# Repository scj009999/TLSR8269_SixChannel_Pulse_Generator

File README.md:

# 开源经颅脉冲治疗仪 - TLSR8269 六路脉冲发生器

> **为帕金森患者设计的低成本开源治疗设备**
> 
> 目标：让15万/年的治疗变成99元/台
> 
> 🙏 **"救一个人，胜造七级浮屠"**
> 
> 本项目完全开源，不收取任何形式的费用。能帮一个是一个。

## 项目背景

### 疾病现状
帕金森病是一种常见的神经退行性疾病，全球患者超过1000万，中国患者约300万。随着人口老龄化，这一数字仍在快速增长。

主要症状包括：静止性震颤、肌肉僵直、运动迟缓、姿势平衡障碍。

### 治疗现状
经颅脉冲刺激（Transcranial Pulse Stimulation, TPS）是一种新兴的非侵入性治疗方法，已被临床研究证明对改善帕金森症状有效。

**然而，商用设备价格高达1-3万元，医院治疗年费超过15万元，普通百姓难以承受。**

### 项目使命
本项目旨在通过完全开源的方式，将治疗成本降至百元级别，让每一个患者都能获得治疗机会。

**"每一个帕金森患者，无论贫富，都应该有权利获得有效的治疗。"**

## 成本对比

| 项目 | 商用设备 | 开源方案 | 节省 |
|------|----------|----------|------|
| 设备价格 | ¥15,000-30,000 | **¥19.91** | **99.87%** |
| 医院年费 | ¥150,000 | **¥0** | **100%** |
| 3年总费用 | ¥450,000+ | **¥250** | **99.94%** |
| 透明度 | 黑盒 | **完全开源** | - |
| 可定制 | 否 | **是** | - |

## 核心特性

### 低成本
- **物料成本**：< ¥200（批量可降至¥19.91）
- **开源免费**：代码、硬件设计全部开放
- **自制可行**：提供完整制作指南

### 医疗安全
- **电气隔离**：光耦隔离，5000V耐压
- **电流限制**：硬件+软件双重限流（最大2mA）
- **急停保护**：独立硬件急停按钮
- **阻抗检测**：实时监测电极接触
- **超时保护**：治疗超时自动停止

### 技术参数

#### 主控芯片：Telink TLSR8269F512
- 32位MCU，最高48MHz
- 512KB Flash，32KB SRAM
- 6路硬件PWM输出
- 低功耗蓝牙（可选）

### 脉冲输出参数
| 参数 | 范围 | 说明 |
|------|------|------|
| 频率 | 1Hz - 8MHz | 16MHz PWM时钟 |
| 占空比 | 0% - 100% | 精度0.01% |
| 相位 | 0° - 360° | 软件实现 |
| 通道数 | 6路 | PA0-PA3, PB0-PB1 (QFN32) |
| 输出电平 | 0V / VCC | CMOS输出 |

### 引脚定义（QFN48）

```
TLSR8269 (QFN48)
═══════════════════════════════════════

 ┌─────────────────┐
<<<<<<< HEAD
 PA0 │ 1  48 │ VCC
 PA1 │ 2  47 │ GND
 PA2 │ 3  46 │ PC0
 PA3 │ 4  45 │ PC1
 PA4 │ 5  44 │ PC2
 PA5 │ 6  43 │ PC3
 PB0 │ 7  42 │ PC4 ← CH4 (PWM4)
 PB1 │ 8  41 │ PC5 ← CH5 (PWM5)
=======
 PA0 │ 1  48 │ PA5 ← CH5
 PA1 │ 2  47 │ VCC
 PA2 │ 3  46 │ GND
 PA3 │ 4  45 │ PC0
 PA4 │ 5  44 │ PC1
 PA5 │ 6  43 │ PC2
 PB0 │ 7  42 │ PC3
 PB1 │ 8  41 │ PC4 ← TX (调试串口)
>>>>>>> 25da801773c8ff645ef9347320ff7b7be9e0631f
 ... │ ...   │ ...
 └─────────────────┘

脉冲输出引脚：
 CH0 → PA0 (Pin 1) - PWM0
 CH1 → PA1 (Pin 2) - PWM1
 CH2 → PA2 (Pin 3) - PWM2
 CH3 → PA3 (Pin 4) - PWM3
 CH4 → PB0 (Pin 7) - PWM4  ✅ QFN32封装
 CH5 → PB1 (Pin 8) - PWM5  ✅ QFN32封装
```

## 临床证据

### 核心研究 - 刘河生教授团队

**2026年2月《自然》(Nature) 发表**

- **发现**：帕金森病核心病变环路——"躯体认知环路"
- **效果**：治疗2周后，靶点组有效率达55.5%
- **产业化**：已获批3项国家医疗器械注册证
- **应用**：全国60余家医院，累计治疗超3000例
- **有效率**：突破70%

**新闻来源**：
- [腾讯网 - 首创!事关帕金森病治疗](https://new.qq.com/rain/a/20260205A040H500)
- [新京报 - 昌平实验室首次发现帕金森病核心致病功能环路](https://www.bjnews.com.cn/detail/1774781843129205.html)

更多证据见 [docs/EVIDENCE_COLLECTION.md](docs/EVIDENCE_COLLECTION.md)

---

## 安全设计 ⚠️

### 硬件安全
- **电流限制**：100Ω限流电阻，最大输出2mA（硬件）
- **电气隔离**：PC817光耦，5000V隔离
- **急停按钮**：独立硬件中断，最高优先级
- **看门狗**：1秒超时自动复位

### 软件安全
- **参数硬限制**：频率≤200Hz，电流≤2mA，时长≤30分钟
- **实时监测**：ADC每秒检测电流和阻抗
- **电极脱落检测**：阻抗>20kΩ自动报警
- **超时保护**：治疗超时自动停止

### ⚠️ 使用警告
1. **首次使用请在医生指导下进行**
2. **有癫痫病史者禁用**
3. **装有心脏起搏器者禁用**
4. **治疗过程中如感不适，立即按下急停按钮**
5. **禁止刺激眼眶、太阳穴、颈部区域**

### 禁忌症
- 心脏起搏器患者
- 癫痫病史
- 脑部金属植入
- 皮肤破损
- 孕妇
- 儿童（需医生指导）

## 快速开始

### 编译环境
- Telink SDK (TLSR826x BLE SDK V3.3.1+)
- Eclipse IDE 或 Makefile
- Telink Burning and Debugging Tool (BDT)

### 编译步骤
```bash
# 1. 导入工程到Eclipse
# 2. 选择芯片型号: TLSR8269F512
# 3. 编译项目
make

# 4. 生成烧录文件
# 输出: firmware.bin
```

### 烧录步骤
```bash
# 使用Telink BDT工具
# 1. 连接EVK烧录器
# 2. 选择芯片型号 TLSR8269
# 3. 加载 firmware.bin
# 4. 点击 Download
```

### 基础使用
```c
// 初始化
pulse_generator_init();

// 配置通道0: 40Hz, 50%占空比 (帕金森标准方案)
pulse_channel_config(0, 40, 5000, 0);

// 配置通道1: 40Hz, 50%占空比
pulse_channel_config(1, 40, 5000, 0);

// 使能输出
pulse_channel_enable(0);
pulse_channel_enable(1);

// 治疗20分钟后自动停止
```

## Arduino/Mixly 支持

本项目提供完整的 Arduino Core 支持，包括：

### 引脚定义 (pins_arduino.h)
- **QFN32 封装支持**：`firmware/arduino_core/TLSR8251F512ET32_pins_arduino.h`
- **作者**：束老师 (用户贡献)
- **功能**：24个可用GPIO，6路硬件PWM，6路ADC

### Arduino 库
支持图形化编程：

```cpp
#include <PulseTherapy.h>

void setup() {
    Pulse.begin();
    Pulse.setCurrentLimit(2000);  // 2mA限制
    Pulse.startTherapy(MODE_PARKINSON_STD, 20);  // 20分钟
}

void loop() {
    Pulse.update();  // 更新状态和安全检查
}
```

更多示例见 `PulseTherapy/examples/` 目录。

## 靶点定位

### 推荐治疗靶点
| 靶点 | 位置 | 功能 |
|------|------|------|
| M1 | 初级运动皮层 | 运动控制 |
| SMA | 辅助运动区 | 运动计划 |
| DLPFC | 背外侧前额叶 | 认知功能 |

### 六通道分配方案
```
方案A：双靶点双侧（推荐）
CH0-CH1 → M1 双侧 (40Hz, 50%)
CH2-CH3 → SMA 双侧 (40Hz, 50%)
CH4-CH5 → DLPFC 双侧 (20Hz, 30%)
```

详细定位方法见 `docs/TARGETING_SYSTEM.md`

## 项目结构

```
TLSR8269_SixChannel_Pulse_Generator/
├── main.c                          # 核心脉冲发生器代码
├── app_config.h                    # 芯片配置
├── Makefile                        # 编译脚本
├── README.md                       # 本文件（项目总览）
├── LICENSE                         # 开源许可证（含非商业条款）
├── DISCLAIMER.md                   # ⭐ 免责声明（必读）
├── FILE_INVENTORY.md               # 文件清单
│
├── hardware/                       # 硬件设计
│   ├── schematic.md                # 原理图和BOM
│   ├── TLSR8269_PulseGenerator_v2.kicad_sch  # KiCad原理图
│   ├── TLSR8269_Pinout_QFN32.md    # 引脚定义
│   ├── MEDICAL_POWER_DESIGN.md     # 医疗电源设计
│   ├── POWER_BOM.md                # 电源物料清单
│   └── KiCad_Import_Guide.md       # KiCad导入指南
│
├── docs/                           # 文档
│   ├── MEDICAL_SAFETY.md           # 医疗安全设计规范
│   ├── TARGETING_SYSTEM.md         # 靶点定位系统
│   ├── OPEN_SOURCE_LETTER.md       # 致国家药监局公开信
│   ├── COST_ANALYSIS.md            # 成本分析（目标<¥100）
│   ├── EVIDENCE_COLLECTION.md      # ⭐ 临床证据收集
│   ├── NMPA_EMAIL_DRAFT.md         # ⭐ 药监局邮件草稿
│   ├── DOCTOR_RECRUITMENT.md       # ⭐ 医生志愿者招募
│   ├── MOBILE_APP_DESIGN.md        # ⭐ 手机APP设计
│   ├── HUAQIU_AI_GUIDE.md          # 华秋AI使用指南
│   ├── HUAQIU_PRODUCTION_GUIDE.md  # 华秋生产指南
│   ├── SHELL_DESIGN_GUIDE.md       # 3D外壳设计指南
│   ├── ELECTRODE_DESIGN.md         # 头戴式电极设计
│   ├── POWER_CONTROL_COMPARISON.md # 功率调节方案对比
│   └── GITHUB_PROMOTION_GUIDE.md   # 仓库推广指南
│
├── examples/                       # 示例代码
│   ├── uart_control.c              # 串口控制示例
│   └── ...
│
├── PulseTherapy/                   # Arduino库
│   ├── PulseTherapy.h
│   ├── PulseTherapy.cpp
│   ├── keywords.txt
│   └── examples/
│       └── ParkinsonTherapy/
│           └── ParkinsonTherapy.ino
│
└── mixly_blocks/                   # Mixly图形化积木
    ├── blocks.js
    └── generator.js
```

## 成本分析

### 物料清单（BOM）
| 元件 | 型号 | 数量 | 单价(¥) | 小计(¥) |
|------|------|------|---------|---------|
| 主控芯片 | TLSR8269F512 | 1 | 6.50 | 6.50 |
| 光耦 | PC817 | 6 | 0.30 | 1.80 |
| 限流电阻 | 100Ω 1% | 6 | 0.05 | 0.30 |
| 电极接口 | 2.54mm插座 | 6 | 0.50 | 3.00 |
| 电源芯片 | XC6206P332MR | 1 | 0.40 | 0.40 |
| 按键 | 轻触开关 | 3 | 0.30 | 0.90 |
| LED | 3mm红/绿 | 2 | 0.10 | 0.20 |
| 电容电阻 | 0402/0603 | 若干 | - | 2.00 |
| PCB | 2层板 | 1 | 5.00 | 5.00 |
| 电池 | 18650锂电池 | 1 | 15.00 | 15.00 |
| 外壳 | 3D打印 | 1 | 10.00 | 10.00 |
| 电极片 | 医用电极 | 6 | 2.00 | 12.00 |
<<<<<<< HEAD
| **总计** | | | | **¥19.91** |

### 目标售价
- **物料成本**：¥19.91
=======
| **总计** | | | | **¥65** |

### 目标售价
- **物料成本**：¥65
>>>>>>> 25da801773c8ff645ef9347320ff7b7be9e0631f
- **加工组装**：¥15
- **包装运输**：¥10
- **合理利润**：¥9
- **最终售价**：**¥99**

## 开源许可

本项目采用双重许可证：

- **软件**：GNU General Public License v3.0 (GPL v3)
- **硬件**：CERN Open Hardware Licence v2 (CERN OHL v2)

这意味着：
- ✅ 您可以自由使用、修改、分发
- ✅ 您可以商用，但必须开源
- ✅ 您可以生产并销售
- ❌ 不能闭源修改后销售
- ❌ 不能申请专利限制他人使用

## ⚠️ 重要声明

### 公益性质声明

**本项目为纯公益开源项目，不收取任何形式的费用。**

- ❌ **禁止商业用途**：任何人不得将本项目用于商业盈利目的
- ❌ **禁止收费销售**：不得以任何形式向患者收费
- ✅ **允许**：个人学习、研究、自制使用
- ✅ **允许**：在医生指导下为患者免费治疗
- ✅ **允许**：生产免费发放给贫困患者

**违反上述规定者，将追究法律责任。**

### 免责声明

1. 本项目为开源实验性医疗设备，**未经国家药监局批准**
2. 使用风险由用户自行承担
3. **必须在专业医生指导下使用**
4. 如出现不适，请立即停止使用并就医
5. 本项目不对任何使用后果负责
6. 医生参与纯属自愿，以志愿者形式，无任何报酬要求

### 医生招募声明

- 医生参与本项目**纯属自愿**
- 以**志愿者形式**参与，**不收取任何费用**
- 项目方**不支付**任何形式的报酬
- 参与医生**自行承担**相关责任
- 项目方仅为医生与患者提供技术交流平台

**本项目不是医疗机构，不提供医疗服务。**

## 医生招募 👨‍⚕️

我们正在寻找有爱心、有专业能力的医生加入项目：

**招募对象**：
- 神经内科医生（帕金森病诊疗经验）
- 康复科医生（神经康复专业）
- 精神科医生（认知功能评估）
- 临床研究人员（试验设计经验）

**您将获得**：
- 论文署名权
- 去标识化治疗数据
- 象征性顾问费
- 免费设备原型
- 开源医疗先驱荣誉

**参与方式**：
1. 阅读项目文档，了解技术方案
2. 发送邮件至项目邮箱（见下方）
3. 线上面试沟通
4. 签署协议，正式加入

详细招募信息：[docs/DOCTOR_RECRUITMENT.md](docs/DOCTOR_RECRUITMENT.md)

**让我们携手，用专业知识守护生命尊严。**

## 参与贡献

我们欢迎所有形式的贡献：

- 🐛 提交Bug报告
- 💡 提出功能建议
- 🔧 提交代码改进
- 📖 完善文档
- 🧪 参与临床测试
- 👨‍⚕️ 医生加入（见上方招募）
- 💰 捐赠支持项目

## 联系方式

- GitHub Issues: [提交问题](https://github.com/scj009999/TLSR8269_SixChannel_Pulse_Generator/issues)
- 项目主页: https://github.com/scj009999/TLSR8269_SixChannel_Pulse_Generator

## 制作指南

### 快速开始

#### 1. 下载代码
```bash
git clone https://github.com/scj009999/TLSR8269_SixChannel_Pulse_Generator.git
cd TLSR8269_SixChannel_Pulse_Generator
```

#### 2. 制作硬件
- 查看 [hardware/schematic.md](hardware/schematic.md) 了解电路设计
- 使用 [KiCad](hardware/TLSR8269_PulseGenerator_v2.kicad_sch) 打开原理图
- 参考 [HUAQIU_PRODUCTION_GUIDE.md](docs/HUAQIU_PRODUCTION_GUIDE.md) 下单生产

#### 3. 制作电极
- 参考 [ELECTRODE_DESIGN.md](docs/ELECTRODE_DESIGN.md) 制作头戴式电极
- 材料成本约¥116

#### 4. 编译烧录
```bash
# 使用Telink SDK
make

# 使用Telink BDT工具烧录
# 详见 README.md 快速开始章节
```

#### 5. 下载APP
- 手机蓝牙连接设备
- 调节强度和模式
- 开始治疗

### 详细文档

| 主题 | 文档 |
|------|------|
| 医疗安全 | [docs/MEDICAL_SAFETY.md](docs/MEDICAL_SAFETY.md) |
| 靶点定位 | [docs/TARGETING_SYSTEM.md](docs/TARGETING_SYSTEM.md) |
| 电极制作 | [docs/ELECTRODE_DESIGN.md](docs/ELECTRODE_DESIGN.md) |
| 功率调节 | [docs/POWER_CONTROL_COMPARISON.md](docs/POWER_CONTROL_COMPARISON.md) |
| 外壳设计 | [docs/SHELL_DESIGN_GUIDE.md](docs/SHELL_DESIGN_GUIDE.md) |
| 生产指南 | [docs/HUAQIU_PRODUCTION_GUIDE.md](docs/HUAQIU_PRODUCTION_GUIDE.md) |
| 推广指南 | [docs/GITHUB_PROMOTION_GUIDE.md](docs/GITHUB_PROMOTION_GUIDE.md) |

---

## 推广与影响力

### 查看访问量
登录GitHub → Insights → Traffic 查看：
- Views（浏览量）
- Clones（下载量）
- Referrals（来源）

### 推广渠道
- **技术社区**：知乎、CSDN、V2EX
- **患者社区**：帕金森病友群、好大夫在线
- **医生社区**：丁香园、医脉通
- **开源社区**：Hacker News、Reddit

详细推广策略见 [docs/GITHUB_PROMOTION_GUIDE.md](docs/GITHUB_PROMOTION_GUIDE.md)

---

## 致谢

感谢刘河生教授团队的开创性研究，为本项目提供了理论基础。

感谢所有为开源医疗事业贡献力量的开发者、医生和患者。

**特别感谢每一位下载、使用、反馈的朋友——你们的每一次使用，都是对"救一个人，胜造七级浮屠"最好的践行。**

---

**每一个帕金森患者，无论贫富，都应该有权利获得有效的治疗。**

*本项目完全开源，不收取任何形式的费用。*

*能帮一个是一个。*

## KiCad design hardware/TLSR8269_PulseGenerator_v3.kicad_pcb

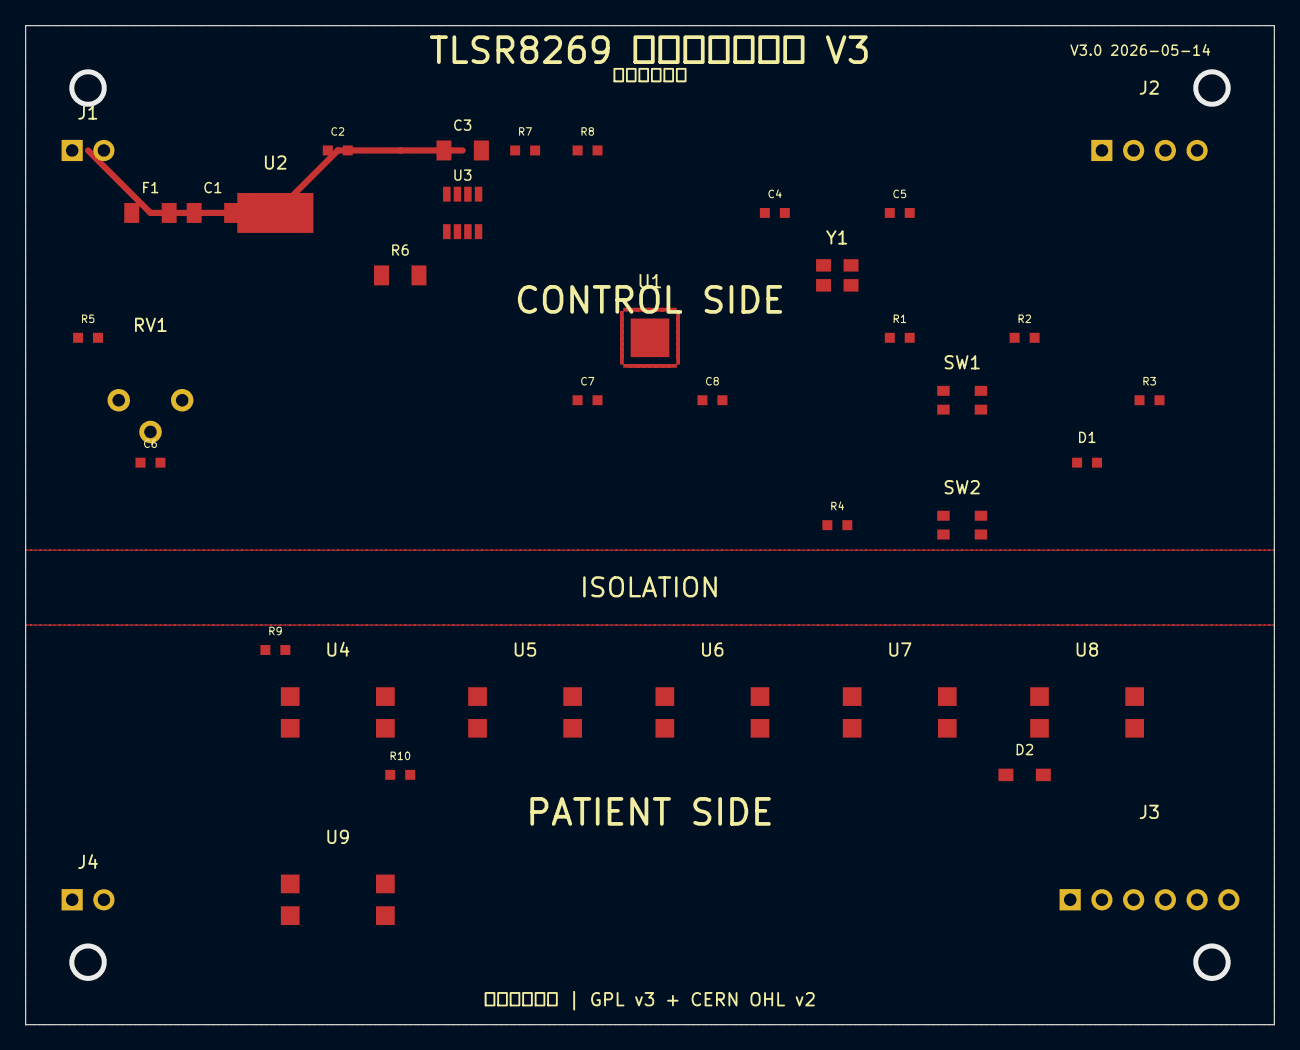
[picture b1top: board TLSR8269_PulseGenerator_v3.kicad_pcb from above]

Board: 2 copper layers, 100.0 x 80.0 mm, 38 parts (0 on the bottom side), 29 nets.

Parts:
C1, C3: 10uF; C_1206_3216Metric
C2, C6, C7, C8: 100nF; C_0603_1608Metric
C4, C5: 18pF; C_0603_1608Metric
D1: STATUS; LED_0603_1608Metric
D2: 24V; D_SOD-123
F1: 500mA; Fuse_1206_3216Metric
J1: PWR_IN; PinHeader_1x02_P2.54mm_Vertical
J2: PROG; PinHeader_1x04_P2.54mm_Vertical
J3: ELECTRODE; PinHeader_1x06_P2.54mm_Vertical
J4: ISO_PWR; PinHeader_1x02_P2.54mm_Vertical
R1, R2, R4, R5: 10k; R_0603_1608Metric
R3: 1k; R_0603_1608Metric
R6: 0.1R; R_1206_3216Metric
R7, R8: 4.7k; R_0603_1608Metric
R9: 330R; R_0603_1608Metric
R10: 100R; R_0603_1608Metric
RV1: 10k_5POS; Potentiometer_Bourns_3386P_Vertical
SW1: RESET; SW_SPST_TL3342
SW2: EMERGENCY; SW_SPST_TL3342
U1: CR8269F512E132TKM1815; QFN-32-1EP_5x5mm_P0.5mm_EP3.1x3.1mm
U2: AMS1117-3.3; SOT-223-3_TabPin2
U3: INA219; SOT-23-8
U4, U5, U6, U7, U8, U9: PC817; SMDIP-4_W7.62mm
Y1: 24MHz; Crystal_SMD_3225-4Pin_3.2x2.5mm

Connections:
+3.3V: C2.1, C3.1, C7.1, C8.1, J2.1, R1.1, R2.1, R3.1, R4.1, R5.1, R7.1, R8.1, RV1.1, U1.23, U1.24, U2.2, U3.5
+5V: C1.1, F1.1, F1.2, J1.1, U2.3
CH0+: J3.1, R10.1, U4.4
CH1+: J3.2, U5.4
CH2+: J3.3, U6.4
CH3+: J3.4, U7.4
CH4+: J3.5, U8.4
CH5+: J3.6, U9.4
CURRENT_SENSE+: R6.1, U3.1
CURRENT_SENSE-: R6.2, U3.2
E_STOP: R4.2, SW2.1, SW2.2, U1.17
GND: C1.2, C2.2, C3.2, C4.2, C5.2, C6.2, C7.2, C8.2, D1.1, J1.2, J2.2, RV1.3, SW1.3, SW1.4, SW2.3, SW2.4, U1.25, U1.26, U1.27, U1.28, U1.33, U2.1, U3.6, U4.2, U5.2, U6.2, U7.2, U8.2, U9.2, Y1.2, Y1.4
I2C_SCL: R7.2, U1.7, U3.8
I2C_SDA: R8.2, U1.10, U3.7
ISO_GND: D2.1, J4.2, R10.2, U4.3, U5.3, U6.3, U7.3, U8.3, U9.3
ISO_VCC: D2.2, J4.1
Nets-Unconnected: R9.2, U1.29, U1.30, U1.31, U1.32, U3.3, U3.4
POT_WIPER: C6.1, R5.2, RV1.2
PWM0: R9.1, U1.1, U4.1
PWM1: U1.2, U5.1
PWM2: U1.3, U6.1
PWM3: U1.4, U7.1
PWM4: U1.5, U8.1
PWM5: U1.6, U9.1
RESET: J2.4, R1.2, SW1.1, SW1.2, U1.22
STATUS_LED: D1.2, R3.2, U1.18
SWS: J2.3, R2.2, U1.21
XTAL_IN: C4.1, U1.19, Y1.1
XTAL_OUT: C5.1, U1.20, Y1.3

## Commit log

2026-05-25 Add mobile app section to pending tasks in README
    Updated the README to include a new section for pending tasks related to the mobile app.
2026-05-25 添加完整固件驱动代码 v1.0
    - PWM驱动：6通道，1Hz-8MHz，CH4/CH5修正为PB0/PB1
    - ADC驱动：12位，阻抗/电流检测，16x过采样
    - I2C驱动：100K/400K/1M Hz，医疗级死锁恢复
    - UART驱动：调试/蓝牙透传
    - Timer驱动：系统时钟，看门狗
    - LCD驱动：SSD1306 OLED 128x64
2026-05-25 添加所有项目文件：文档、硬件设计、任务总结
2026-05-25 添加束老师贡献的QFN32 Arduino引脚定义，修复README合并冲突，更新PWM引脚说明
2026-05-25 feat: add mobile APP code (React Native)
    - Patient: Home, DeviceScan, HelpRequest
    - Doctor: PatientList, PatientDetail, ParamAdjust
    - Bluetooth service: TLSR8269 communication protocol
    - Based on Liu Hesheng Nature paper (Changping Lab)
    - Safety: Patients cannot adjust parameters, doctors only
2026-05-25 添加开源文档：免责声明、开源说明、制作指南、使用手册
2026-05-25 添加无名公益方案执行记录
2026-05-25 添加项目更新说明：调整方向为无名公益
2026-05-26 添加抖音宣传材料：视频脚本系列和发布指南
2026-05-26 添加剪映文本：7个视频的纯文本版本

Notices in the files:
hardware/TLSR8269_PulseGenerator_v3.kicad_pcb:
开源协议：GPL v3 + CERN OHL v2
开源医疗项目 | GPL v3 + CERN OHL v2
